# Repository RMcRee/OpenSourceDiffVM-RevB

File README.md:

# Who is responsible
```
Schematic by Randall McRee 
PCB layout by Krasimir Kostadinov 
Software mostly from Claude 
```

# OpenSourceDiffVM-RevB

A high-resolution differential voltmeter (8.5-9.5 digit) with nanovolt-level sensitivity, based on the Analog Devices article on [low-noise instrumentation amplifiers](https://www.analog.com/en/resources/analog-dialogue/articles/low-noise-inamp-nanovolt-sensitivity.html).

## How It Works

An unknown voltage Vx is compared against a precision 16-bit DAC using a chopped measurement topology. The DAC output tracks Vx to within a few millivolts, and a high-gain instrumentation amplifier amplifies the residual difference for digitization by a 24-bit ADC. Chopping at ~385 Hz cancels preamp offset and 1/f noise.

```
Unknown Vx ──┐
             ├──[TMUX SPDT]──► AD8428 x4 ──► ADS127L11 ──► Teensy 4.x
DAC Output ──┘   (chopped)    (×2000 gain)   (24-bit ADC)
```

**Measurement equation:** `Vx = DAC_voltage + (ADC_mean / preamp_gain) × divider_ratio`

The DAC is calibrated against three ADR1001 ultra-stable voltage references (0.05 ppm/C) with 1000+ hour burn-in. Real-time drift compensation tracks the reference filter lag.

## Key Components

| Component | Function |
|-----------|----------|
| 4x AD8428 | Ultra-low-noise instrumentation amplifier (1.5 nV/rtHz), gain = 2000 |
| TMUX7234 | Low-charge-injection SPDT switches for input chopping |
| ADS127L11 | 24-bit delta-sigma ADC, ~3906 SPS |
| AD5760 | 16-bit precision DAC, tracks unknown input |
| 3x ADR1001 | Ultra-stable voltage references, filtered and averaged |
| Teensy 4.1 | ARM Cortex-M7 @ 600 MHz, hardware 64-bit double |

## Voltage Ranges

| Range | Method | Resolution |
|-------|--------|------------|
| +/-5V | Direct input | ~0.15 nV/count |
| +/-50V | Caddock 1776-C4815 divider (1:10, hardwired) | ~1.5 nV |
| +/-500V | Parallel tap (1:108.76) | ~16 nV |
| +/-5kV | Parallel tap (1:984.65) | ~150 nV |

## Firmware

The firmware runs on Teensy 4.1 and provides:

- **Serial command interface** over USB (115200 baud) — type `help` for commands
- **Channel scanning** — configure a scan list of up to 7 input channels
- **Three output modes** — human-readable, CSV for logging, Arduino Serial Plotter
- **Configurable integration** — 10 to 10,000 chop cycles per reading
- **Auto-zero** — periodic GND measurement for offset tracking
- **Reference drift compensation** — real-time prediction of filter lag error
- **DAC auto-adjustment** — binary search to keep preamp in range
- **Power-on self-test** — 9 hardware verification tests
- **EEPROM persistence** — save/load configuration across power cycles

### Building

Requires [Teensy board support](https://www.pjrc.com/teensy/td_download.html) for Arduino.

```bash
# Arduino CLI
arduino-cli compile --fqbn teensy:avr:teensy41 OpenSourceDiffVM-RevB.ino
arduino-cli upload --fqbn teensy:avr:teensy41 -p COM_PORT OpenSourceDiffVM-RevB.ino
```

### Serial Commands

Connect at 115200 baud. Key commands:

```
scan add Vx          # Add channel to scan list
scan add VrefRaw     # Add another channel
scan start           # Begin scanning
scan stop            # Stop scanning
log start            # Switch to CSV output
plot start           # Switch to Serial Plotter output
integrate 200        # Set 200 chop cycles per reading
autozero on          # Enable periodic zero calibration
range 100            # Set HV divider to +/-500V
zero                 # Immediate zero calibration
status               # Show current configuration
config save          # Persist to EEPROM
help                 # List all commands
```

### CSV Output Format

```
# timestamp_ms,channel,voltage_V,uncertainty_V,stddev_counts,mean_counts,n,dac_code,drift_ppb
123456,Vx,1.234567890123e-03,1.230000000000e-09,8.234,12345.678,100,12345,5.060
```

## PC Companion Script

`tools/diffvm.py` provides host-side functionality:

```bash
pip install pyserial matplotlib pyyaml

# Interactive terminal
python tools/diffvm.py --port COM3

# Configure from file and start scanning
python tools/diffvm.py --port COM3 --config tools/diffvm_config.yaml

# Log CSV to disk
python tools/diffvm.py --port COM3 --config tools/diffvm_config.yaml --log ./logs

# Live matplotlib plot
python tools/diffvm.py --port COM3 --config tools/diffvm_config.yaml --plot

# Full operation: config + log + plot
python tools/diffvm.py --port COM3 --config tools/diffvm_config.yaml --log ./logs --plot
```

See `tools/diffvm_config.yaml` for configuration options.

## Hardware Design

KiCad 8 project files are in `DiffVM/`:

| File | Description |
|------|-------------|
| `DiffVM_4L.kicad_sch` | Root schematic (4-layer PCB) |
| `FrontEnd.kicad_sch` | TMUX switches, AD8428 preamp chain, AD5760 DAC |
| `DAC.kicad_sch` | ADS127L11 ADC and Teensy interface |
| `VRef.kicad_sch` | 3x ADR1001 voltage references |
| `DiffVM_4L.kicad_pcb` | PCB layout |

## Design Notes

| Document | Description |
|----------|-------------|
| [`filter-design.md`](filter-design.md) | Workflow for building precision low-pass filters with measured capacitors and calculated resistors |
| [`Calibration.md`](Calibration.md) | Calibration procedures and constants |
| [`ADC_analysis.md`](ADC_analysis.md) | ADS127L11 configuration, filter selection, and ENOB analysis |

## References

- [Low-Noise Instrumentation Amplifier with Nanovolt Sensitivity](https://www.analog.com/en/resources/analog-dialogue/articles/low-noise-inamp-nanovolt-sensitivity.html) (Analog Devices)
- [AD8428 datasheet](https://www.analog.com/media/en/technical-documentation/data-sheets/AD8428.PDF)
- [ADS127L11 datasheet](https://www.ti.com/lit/ds/symlink/ads127l11.pdf)
- [AD5760 datasheet](https://www.analog.com/media/en/technical-documentation/data-sheets/AD5760.pdf)

## License

Licensed under the [CERN Open Hardware Licence Version 2 - Permissive](LICENSE) (CERN-OHL-P v2).

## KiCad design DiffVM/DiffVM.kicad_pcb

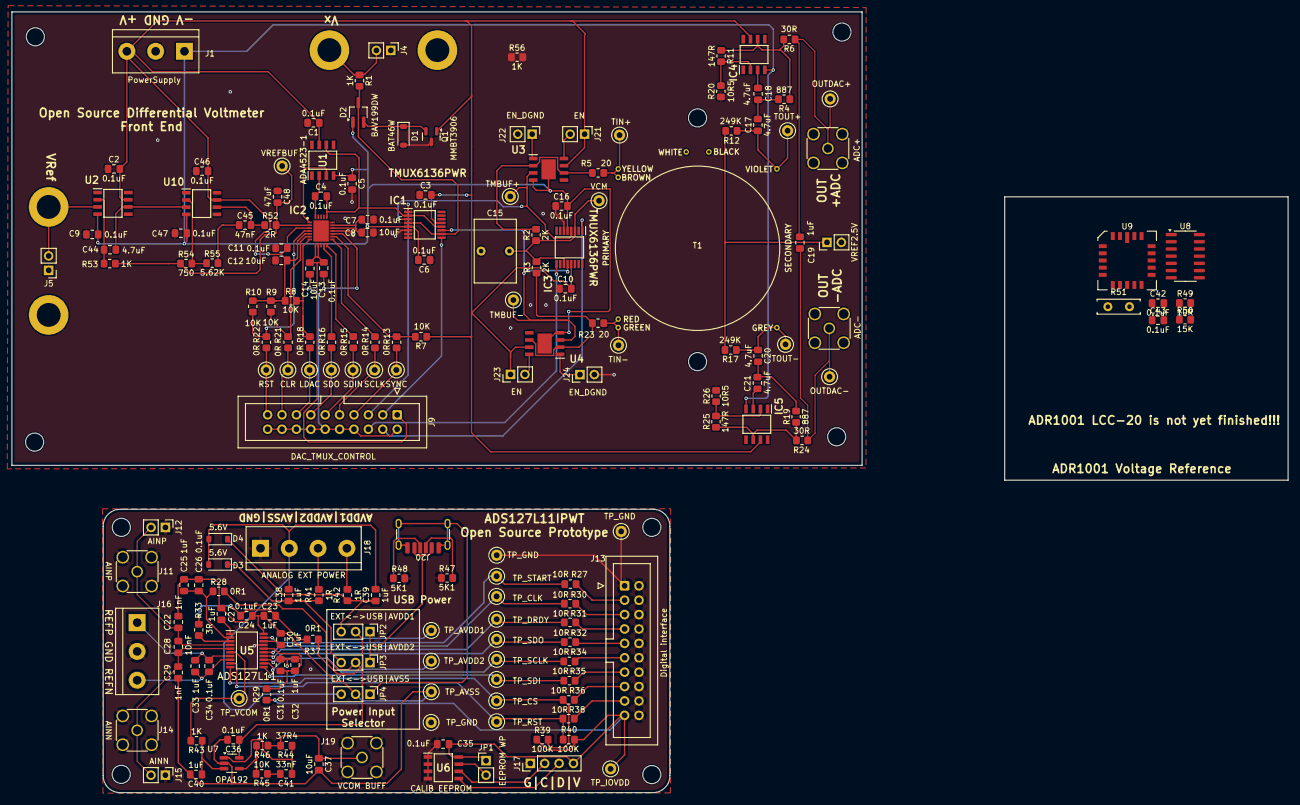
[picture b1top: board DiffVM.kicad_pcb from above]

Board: 2 copper layers, 225.2 x 137.8 mm, 197 parts (0 on the bottom side), 116 nets.

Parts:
C1, C2, C3, C4, C5, C6, C7, C9, C10, C11, C13, C16, C24, C26, C31, C34, C35, C36, C42, C43, C46, C47: 0.1uF; C_0805_2012Metric_Pad1.18x1.45mm_HandSolder
C8, C12, C14, C37: 10uF; C_0805_2012Metric_Pad1.18x1.45mm_HandSolder
C15: 10uF; C_Rect_L7.2mm_W11.0mm_P5.00mm_FKS2_FKP2_MKS2_MKP2
C17, C18, C20, C21, C44: 4.7uF; C_0805_2012Metric_Pad1.18x1.45mm_HandSolder
C19, C23, C25, C27, C30, C32, C33, C38, C39, C40: 1uF; C_0805_2012Metric_Pad1.18x1.45mm_HandSolder
C22, C29: 1nF; C_0805_2012Metric_Pad1.18x1.45mm_HandSolder
C28: 10nF; C_0805_2012Metric_Pad1.18x1.45mm_HandSolder
C41: 33nF; C_0805_2012Metric_Pad1.18x1.45mm_HandSolder
C45: 47nF; C_0805_2012Metric_Pad1.18x1.45mm_HandSolder
C48: 47uF; C_0805_2012Metric_Pad1.18x1.45mm_HandSolder
D1: BAT46W; D_SOD-123
D2: BAV199DW; TSOT-23_HandSoldering
D3, D4: 5.6V; D_SOD-123
H1, H2, H3, H4, H5, H6, H7, H8, H9, H10: MountingHole; MountingHole_3.2mm_M3_DIN965
IC1, IC3: TMUX6136PWR; SOP65P640X120-16N
IC2: AD5760BCPZ; QFN50P400X500X100-25N-D
IC4, IC5: AD797; SOIC127P600X175-8N
J1: PowerSupply; TerminalBlock_bornier-3_P5.08mm
J2, J3, J6, J7: BindingPost; Binding_Post_4.2mm
J4: Vx; PinHeader_1x02_P2.54mm_Vertical
J5: VRef; PinHeader_1x02_P2.54mm_Vertical
J8: ADC+; SMA_Wurth_60312002114503_Vertical
J9: DAC_TMUX_CONTROL; IDC-Header_2x10_P2.54mm_Vertical
J10: ADC-; SMA_Wurth_60312002114503_Vertical
J11: AINP; SMA_Wurth_60312002114503_Vertical
J12: AINP; PinHeader_1x02_P2.54mm_Vertical
J13: Digital interface; IDC-Header_2x10_P2.54mm_Vertical
J14: AINN; SMA_Wurth_60312002114503_Vertical
J15: AINN; PinHeader_1x02_P2.54mm_Vertical
J16: VREF; TerminalBlock_bornier-3_P5.08mm
J17: CALIB EEPROM; PinHeader_1x04_P2.54mm_Vertical
J18: ANALOG EXT POWER; TerminalBlock_bornier-4_P5.08mm
J19: VCOM BUFF; SMA_Wurth_60312002114503_Vertical
J20: USB_C_Receptacle_PowerOnly_6P; USB_C_Receptacle_MOLEX_217175-0001_6P_TopMnt_Horizontal
J21, J23: EN; PinHeader_1x02_P2.54mm_Vertical
J22, J24: EN_DGND; PinHeader_1x02_P2.54mm_Vertical
J25: VREF2.5V; PinHeader_1x02_P2.54mm_Vertical
JP1: EEPROM WP; PinHeader_1x02_P2.54mm_Vertical
JP2: EXT<->USB|AVDD1; PinHeader_1x03_P2.54mm_Vertical
JP3: EXT<->USB|AVDD2; PinHeader_1x03_P2.54mm_Vertical
JP4: EXT<->USB|AVSS; PinHeader_1x03_P2.54mm_Vertical
Q1: MMBT3906; SOT-23
R1, R43, R46, R53, R56: 1K; R_0805_2012Metric_Pad1.20x1.40mm_HandSolder
R2, R3: 2K; R_0805_2012Metric_Pad1.20x1.40mm_HandSolder
R4, R19: 887; R_0805_2012Metric_Pad1.20x1.40mm_HandSolder
R5, R23: 20; R_0805_2012Metric_Pad1.20x1.40mm_HandSolder
R6, R24: 30R; R_0805_2012Metric_Pad1.20x1.40mm_HandSolder
R7, R8, R9, R10, R45: 10K; R_0805_2012Metric_Pad1.20x1.40mm_HandSolder
R11, R25: 147R; R_0805_2012Metric_Pad1.20x1.40mm_HandSolder
R12, R17: 249K; R_0805_2012Metric_Pad1.20x1.40mm_HandSolder
R13, R14, R15, R16, R18, R21, R22: 0R; R_0805_2012Metric_Pad1.20x1.40mm_HandSolder
R20, R26: 10R5; R_0805_2012Metric_Pad1.20x1.40mm_HandSolder
R27, R30, R31, R32, R34, R35, R36, R38, R49: 10R; R_0805_2012Metric_Pad1.20x1.40mm_HandSolder
R28, R29, R37: 0R1; R_0805_2012Metric_Pad1.20x1.40mm_HandSolder
R33: 3R; R_0805_2012Metric_Pad1.20x1.40mm_HandSolder
R39, R40: 100K; R_0805_2012Metric_Pad1.20x1.40mm_HandSolder
R41, R42: 1R; R_0805_2012Metric_Pad1.20x1.40mm_HandSolder
R44: 37R4; R_0805_2012Metric_Pad1.20x1.40mm_HandSolder
R47, R48: 5K1; R_0805_2012Metric_Pad1.20x1.40mm_HandSolder
R50: 15K; R_0805_2012Metric_Pad1.20x1.40mm_HandSolder
R51: 120R; Vishay_L7.62mm_D2.67mm_P3.81_5.08mm_Horizontal
R52: 2R; R_0805_2012Metric_Pad1.20x1.40mm_HandSolder
R54: 750; R_0805_2012Metric_Pad1.20x1.40mm_HandSolder
R55: 5.62K; R_0805_2012Metric_Pad1.20x1.40mm_HandSolder
T1: Transformer_1P_1S; CMQEE-3440A
TP1: VREFBUF; TestPoint_Keystone_5269
TP2: OUTDAC+; TestPoint_Keystone_5269
TP3: TIN+; TestPoint_Keystone_5269
TP4: TOUT+; TestPoint_Keystone_5269
TP5: TIN-; TestPoint_Keystone_5269
TP6: TOUT-; TestPoint_Keystone_5269
TP7: OUTDAC-; TestPoint_Keystone_5269
TP8: TP_START; TestPoint_Keystone_5269
TP9: TP_CLK; TestPoint_Keystone_5269
TP10: TP_DRDY; TestPoint_Keystone_5269
TP11: TP_SDO; TestPoint_Keystone_5269
TP12: TP_SCLK; TestPoint_Keystone_5269
TP13: TP_SDI; TestPoint_Keystone_5269
TP14: TP_CS; TestPoint_Keystone_5269
TP15: TP_RST; TestPoint_Keystone_5269
TP16, TP17, TP18: TP_GND; TestPoint_Keystone_5269
TP19: TP_AVSS; TestPoint_Keystone_5269
TP20: TP_AVDD1; TestPoint_Keystone_5269
TP21: TP_AVDD2; TestPoint_Keystone_5269
TP22: TP_VCOM; TestPoint_Keystone_5269
TP23: TP_IOVDD; TestPoint_Keystone_5269
TP24: TMBUF+; TestPoint_Keystone_5269
TP25: TMBUF-; TestPoint_Keystone_5269
TP26: SYNC; TestPoint_Keystone_5269
TP27: SCLK; TestPoint_Keystone_5269
TP28: SDIN; TestPoint_Keystone_5269
TP29: SDO; TestPoint_Keystone_5269
TP30: LDAC; TestPoint_Keystone_5269
TP31: CLR; TestPoint_Keystone_5269
TP32: RST; TestPoint_Keystone_5269
TP33: VCM; TestPoint_Keystone_5269
U1, U2: ADA4523-1; SOIC127P600X175-8N
U3, U4: LT6018; SOIC127P599X175-9N
U5: ADS127L11IPWT; SOP65P640X120-20N
U6: 24LC00; SOIC127P600X175-8N
U7: OPA192; SOT-23-5_HandSoldering
U8: ADA4522-4; SOIC-14_3.9x8.7mm_P1.27mm
U9: ADR1001; LCC-20
U10: LT6202; SOIC127P600X175-8N

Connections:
+3.3V: C35.1, J13.19, J17.4, JP1.1 (A), R29.2, R39.1, R40.1, TP23.1, U6.8 (VCC)
+VDC: C1.1, C2.2, C3.2, C10.2, C11.1, C12.1, C42.1, C46.2, IC1.13 (VDD), IC2.3 (VDD_1), IC2.5 (VDD_2), IC3.13 (VDD), IC4.7 (V+), IC5.7 (V+), J1.3, J21.1, J23.1, Q1.1 (B), R7.1, R8.1, R9.1, R10.1, U1.7 (V+), U2.7 (V+), U3.7 (V+), U4.7 (V+), U9.18 (HTR_IN), U9.19 (VIN), U10.7 (V+)
-VDC: C5.1, C6.2, C7.1, C8.1, C9.1, C16.2, C47.1, D2.1 (A1), IC1.5 (VSS), IC2.17 (VSS_1), IC2.18 (VSS_2), IC3.5 (VSS), IC4.4 (V-), IC5.4 (V-), J1.1, U1.4 (V-), U2.4 (V-), U3.4 (V-), U3.9 (EP), U4.4 (V-), U4.9 (EP), U10.4 (V-)
ADC+: C19.2, J8.1 (In), R6.2, TP2.1
ADC-: C19.1, J10.1 (In), R24.2, TP7.1
AINN: C28.2, C29.2, J14.1 (In), J15.2, U5.5 (AINN)
AINP: C22.1, C28.1, J11.1 (In), J12.2, U5.4 (AINP)
AVDD1: C36.1, JP2.2 (C), R37.1, TP20.1, U7.5 (V+)
AVDD2: JP3.2 (C), R28.2, TP21.1
AVSS: C22.2, C23.1, C24.1, C25.1, C26.1, C27.1, C29.1, C30.1, C36.2, C37.2, C40.2, JP4.2 (C), TP19.1, U5.20 (AVSS), U7.2 (V-)
CI_TMUXSEL1: IC3.1 (SEL1), J9.4
CI_TMUXSEL2: IC3.9 (SEL2), J9.6
CLK_DAC: R30.1, TP9.1, U5.15 (CLK)
CLR_VREF_DAC: IC2.6 (~CLR), R9.2, R21.2
CS_DAC: R36.1, R39.2, TP14.1, U5.10 (~CS)
DRDY_DAC: R31.1, TP10.1, U5.14 (~DRDY)
EXT_AVDD1: C39.1, D4.1 (K), JP2.3 (B), R42.2
EXT_AVDD2: C38.1, D3.1 (K), JP3.3 (B), R41.2
EXT_AVSS: C38.2, C39.2, D3.2 (A), D4.2 (A), J18.2, JP4.3 (B)
GND: C1.2, C2.1, C3.1, C5.2, C6.1, C7.2, C8.2, C9.2, C10.1, C11.2, C12.2, C15.1, C16.1, C31.2, C32.2, C35.2, C42.2, C43.2, C46.1, C47.2, C48.1, D1.2 (A), IC1.6 (GND), IC2.16 (VREFN), IC2.19 (AGND), IC3.6 (GND), J1.2, J4.1, J5.1, J6.1, J7.1, J8.2 (Ext), J10.2 (Ext), J11.2 (Ext), J12.1, J13.1, J13.2, J13.4, J13.6, J13.8, J13.10, J13.12, J13.14, J13.16, J13.18, J13.20, J14.2 (Ext), J15.1, J16.2, J17.1, J18.1, J19.2 (Ext), J22.2, J24.2, J25.2, Q1.3 (C), R20.2, R26.2, R47.1, R48.1, R49.2, TP16.1, TP17.1, TP18.1, U5.17 (DGND), U6.1 (A0), U6.2 (A1), U6.3 (A2), U6.4 (GND), U9.16 (HTR_GND)
GNDD: C13.2, C14.2, IC2.15 (DGND), J9.2, J9.8, J9.10, J9.12, J9.14, J9.16, J9.18, J9.20
GNDREF: R51.2, U9.8 (INV1), U9.13 (BUF_GND), U9.14 (REF_GND), U9.15 (REF_GND)
IOVCC: C13.1, C14.1, IC2.8 (VCC), IC2.9 (IOVCC), J9.1
LDAC_VREF_DAC: IC2.7 (~LDAC), R8.2, R18.2
unnamed: C17.2, C18.1, R4.2
unnamed: C20.2, C21.1, R19.2
unnamed: C23.2, C24.2, R33.1, R37.2
unnamed: C41.1, R44.2, U7.1
unnamed: C41.2, R45.1
unnamed: C45.1, R55.2
unnamed: C45.2, R52.1, U10.6
unnamed: D1.1 (K), D2.2 (K2), Q1.2 (E), R56.2
unnamed: D2.3 (K3A4), IC1.4 (S1B), IC1.10 (S2A), R1.2
unnamed: C4.1, IC2.24 (INV), U1.2 (-)
unnamed: C48.2, IC2.2 (VREFP), R52.2, R53.2, R54.1, TP1.1
unnamed: C15.2, IC3.3 (D1), IC3.11 (D2), R2.1, R3.2, TP33.1
unnamed: C18.2, IC4.3 (+)
unnamed: IC4.2 (-), R11.2, R20.1
unnamed: IC4.6, R4.1, R6.1, R11.1
unnamed: C21.2, IC5.3 (+)
unnamed: IC5.2 (-), R25.2, R26.1
unnamed: IC5.6, R19.1, R24.1, R25.1
unnamed: J2.1, J4.2, R1.1, R56.1
unnamed: J9.7, R13.1, TP26.1
unnamed: J9.9, R14.1, TP27.1
unnamed: J9.11, R15.1, TP28.1
unnamed: J9.13, R16.1, TP29.1
unnamed: J9.15, R18.1, TP30.1
unnamed: J9.17, R21.1, TP31.1
unnamed: J9.19, R22.1, TP32.1
unnamed: J13.3, R27.2
unnamed: J13.5, R30.2
unnamed: J13.7, R31.2
unnamed: J13.9, R32.2
unnamed: J13.11, R34.2
unnamed: J13.13, R35.2
unnamed: J13.15, R36.2
unnamed: J13.17, R38.2
unnamed: J18.3, R41.1
unnamed: J18.4, R42.1
unnamed: J20.A5 (CC1), R47.2
unnamed: J20.B5 (CC2), R48.2
unnamed: J21.2, U3.8 (EN)
unnamed: J22.1, U3.1 (DGND)
unnamed: J23.2, U4.8 (EN)
unnamed: J24.1, U4.1 (DGND)
unnamed: JP1.2 (B), U6.7 (WP)
unnamed: R5.2, T1.1 (AA), TP3.1
unnamed: R23.2, T1.2 (AB), TP5.1
unnamed: C20.1, R17.2, T1.3 (SA), TP6.1
unnamed: C17.1, R12.2, T1.4 (SB), TP4.1
unnamed: C44.2, R53.1, U2.2 (-)
unnamed: R33.2, U5.3 (AVDD1)
unnamed: C25.2, C26.2, R28.1, U5.2 (AVDD2)
unnamed: C27.2, U5.1 (CAPA)
unnamed: C30.2, U5.18 (CAPD)
unnamed: C31.1, C32.1, R29.1, U5.16 (IOVDD)
unnamed: C40.1, R43.1, U7.3 (+)
unnamed: R45.2, R46.2, U7.4 (-)
unnamed: U8.10 (+), U9.7 (INV2)
unnamed: U9.10 (VDOUT), U9.11 (BUF_INP)
unnamed: R49.1, U9.17 (HTR_ILIM)
unnamed: R51.1, U9.1 (ISET)
unnamed: R50.1, U9.20 (PWRGD)
unnamed: U9.4 (REF6P6_F), U9.5 (REF6P6_S), U9.6 (VDIN)
unnamed: C44.1, U2.6, U10.3 (+)
unnamed: R54.2, R55.1, U10.2 (-)
REFN: C33.2, C34.2, J16.3, U5.8 (REFN)
REFP: C33.1, C34.1, J16.1, U5.7 (REFP)
RESET_DAC: R38.1, R40.2, TP15.1, U5.9 (~RESET)
RESET_VREF_DAC: IC2.4 (~RESET), R10.2, R22.2
SCL: J17.2, U6.6 (SCL)
SCLK_DAC: R34.1, TP12.1, U5.12 (SCLK)
SCLK_VREF_DAC: IC2.13 (SCLK), R14.2
SDA: J17.3, U6.5 (SDA)
SDIN_VREF_DAC: IC2.12 (SDIN), R15.2
SDI_DAC: R35.1, TP13.1, U5.11 (SDI)
SDO_DAC: R32.1, TP11.1, U5.13 (SDO/~DRDY)
SDO_VREF_DAC: IC2.11 (SDO), R16.2
START_DAC: R27.1, TP8.1, U5.19 (START)
SYNC_VREF_DAC: IC2.14 (~SYNC), R7.2, R13.2
TMUXOUT1: IC1.3 (D1), IC3.4 (S1B), TP24.1, U3.3 (+)
TMUXOUT2: IC1.11 (D2), IC3.12 (S2B), TP25.1, U4.3 (+)
TMUXSEL1: IC1.1 (SEL1), J9.5
TMUXSEL2: IC1.9 (SEL2), J9.3
TMUX_BUF_OUT1: R2.2, R5.1, U3.2 (-), U3.6
TMUX_BUF_OUT2: R3.1, R23.1, U4.2 (-), U4.6
USB_AVDD: J20.A9 (VBUS), J20.B9 (VBUS), JP2.1 (A), JP3.1 (A)
USB_GND: J20.A12 (GND), J20.B12 (GND), J20.S1 (SHIELD), JP4.1 (A)
VCOM: R43.2, TP22.1, U5.6 (VCM)
VCOM_BUFF: C37.1, J19.1 (In), R44.1, R46.1
VRef: J3.1, J5.2, U2.3 (+)
VRef2.5V: J25.1, R12.1, R17.1, U8.8, U8.9 (-)
VRef5V: C43.1, U9.9 (BUF_S), U9.12 (BUF_F)
VRefDAC2xOut: C4.2, IC1.2 (S1A), IC1.12 (S2B), IC2.20 (RFB), U1.6
VRefDACOut: IC2.1 (VOUT), U1.3 (+)

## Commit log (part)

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2026-02-24 Update HV_Divider_Prototype_Schematic.txt
    Uses an OPA828 for HV buffer.
2026-04-30 Rewrite signal-chain POST tests to use chop-demod with binary-searched null
    The signal_chain, polarity, and chop_symmetry POST tests were validating
    single-phase ADC reads against the input chain at gain x2000, which always
    rails on a healthy unit because the chain has a natural ~262 uV RTI residual
    offset (auto-zero compensates this in normal operation). Rewritten:
    - signal_chain runs binarySearchDAC() on GND input to find the per-unit null,
    caches it in s_postZeroDac, and validates the chopped demod is sane
2026-05-04 minor changes to tweak ADC sampling to tune in minimal allen variance
2026-05-04 fix off-by-1 error in calc of allen variance
2026-05-08 Add Huber-clipped pooled-MAD outlier handling in demodulate()
    Replaces per-cycle hard rejection with Huber soft-clipping over a 256-deep
    pooled-MAD threshold; pool resets on any DAC code change or input mux switch
    so step transitions don't bias the next ~21 chop cycles toward the previous
    signal level. Runtime knob 'drj <k>' tunes clip threshold (k=10000 disables).
    Empirically eliminates the long-tau ADEV regression seen with hard rejection
    (rej-ON 1.4x worse at tau=960s) while preserving the short-tau noise win.
